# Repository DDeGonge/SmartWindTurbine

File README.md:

# SmartWindTurbine
A 3D powerful printed wind turbine generator featuring onboard wind telemetry, automatic blade pitch and direction adjustments, and power monitoring. It's overkill, just because.

CAD files are located on [Onshape](https://cad.onshape.com/documents/081a1df8703679f22d54e44e/w/6e7545ad57ad37421d013d4d/e/d723b20ba07c82c17beb4b5e?renderMode=0&uiState=63444fee8be634087e92f6b6)

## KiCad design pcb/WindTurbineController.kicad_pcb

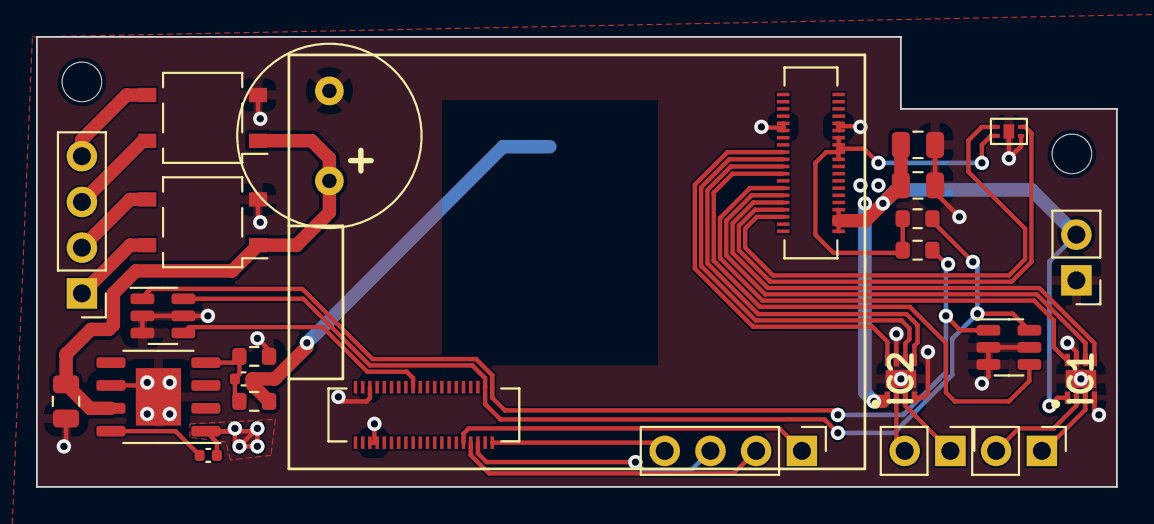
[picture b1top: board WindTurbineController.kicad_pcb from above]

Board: 2 copper layers, 60.0 x 25.0 mm, 27 parts (1 on the bottom side), 27 nets.

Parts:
C1: 220uF; C_Radial_D10.0mm_H16.0mm_P5.00mm
C2, C3, C6: 10uF; C_0805_2012Metric
C4: 82pF; C_0402_1005Metric
C5: 10nF; C_0402_1005Metric
D1, D2: D_Bridge_+-AA; TO-269AA
IC1, IC2: DRV8220DSGR; SON50P200X200X80-9N
J1, J2, J4: Conn_01x02; PinHeader_1x02_P2.54mm_Vertical
J3, J5: Conn_01x04; PinHeader_1x04_P2.54mm_Vertical
J6, J7: Conn_01x01; MountingHole_2.2mm_M2
L1: 32.5uH; PCC-M105xx
R1, R2, R4: 11.3k; R_0603_1608Metric
R3: 100k; R_0603_1608Metric
U1: MUBv1; MUB_v1
U2, U3: TLV493D; SOT-23-6
U4: AH1388; X2-DFN1410-4
U5: RT8279GSP; SOIC-8-1EP_3.9x4.9mm_P1.27mm_EP2.514x3.2mm

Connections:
+3V3: R1.1, R2.1, U1.62 (3v3), U1.64 (3v3), U1.66 (3v3), U1.68 (3v3), U4.1 (VDD)
+12V: C2.1, C3.1, C4.2, IC1.1 (VM), IC2.1 (VM), J4.2, L1.1, R3.1, U1.42 (Vin), U1.44 (Vin), U1.46 (Vin), U1.48 (Vin)
+VDC: C1.1, C6.1, D1.1 (+), D2.1 (+), U5.7 (VIN)
/HS_N: U1.45 (GPIO15), U4.4 (OUT1)
/HS_S: U1.47 (GPIO14), U4.3 (OUT2)
/IND_IN: C5.1, L1.2, U5.1 (BOOT)
/M0_EN0: IC1.5 (IN2/EN), U1.49 (GPIO13)
/M0_EN1: IC1.6 (IN1/PH), U1.51 (GPIO12)
/M0_SLEEP: IC1.8 (NSLEEP), U1.53 (GPIO11)
/M1_EN0: IC2.5 (IN2/EN), U1.59 (GPIO8)
/M1_EN1: IC2.6 (IN1/PH), U1.61 (GPIO7)
/M1_SLEEP: IC2.8 (NSLEEP), U1.63 (GPIO6)
/SCL: R2.2, U1.39 (SCL), U2.1 (SCL/INT), U3.1 (SCL/INT)
/SDA: R1.2, U1.37 (SDA), U2.6 (SDA/ADDR), U3.6 (SDA/ADDR)
/TLV0_POWER: U1.57 (GPIO9), U2.4 (VDD)
/TLV1_POWER: U1.17 (GPIO27), U3.4 (VDD)
GND: C1.2, C2.2, C3.2, C6.2, D1.2 (-), D2.2 (-), IC1.4 (GND), IC1.7 (MODE), IC1.9 (EP), IC2.4 (GND), IC2.7 (MODE), IC2.9 (EP), J4.1, R4.2, U1.5 (gnd), U1.6 (gnd), U1.8 (gnd), U1.69 (gnd), U1.70 (gnd), U1.71 (gnd), U1.72 (gnd), U2.2 (GND), U2.3 (GND), U2.5 (GND), U3.2 (GND), U3.3 (GND), U3.5 (GND), U4.2 (GND), U5.6 (GND), U5.9 (EPAD)
unnamed: D1.4, J3.1
unnamed: D1.3, J3.2
unnamed: D2.4, J3.3
unnamed: D2.3, J3.4
unnamed: J5.1, U1.32 (GPIO20)
unnamed: J5.2, U1.34 (GPIO19)
unnamed: J5.3, U1.36 (GPIO18)
unnamed: J5.4, U1.40 (GPIO17)
unnamed: C4.1, R3.2, R4.1, U5.4 (FB)
unnamed: C5.2, U5.8 (SW)

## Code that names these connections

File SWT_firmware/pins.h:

#define TLV0_PWR 9
#define TLV1_PWR 27

#define HS_S 14
#define HS_N 15

#define M1_EN0 13
#define M1_EN1 12
#define M1_SLEEP 11

#define M0_EN0 8
#define M0_EN1 7
#define M0_SLEEP 6

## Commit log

2023-01-07 all of the work
2023-02-04 fixes
